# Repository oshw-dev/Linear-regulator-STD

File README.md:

# Linear-regulator-STD
Standard linear regulator

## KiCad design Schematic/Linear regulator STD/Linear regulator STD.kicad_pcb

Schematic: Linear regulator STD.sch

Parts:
C1, C3: 22uF; CP_EIA-3528-15_AVX-H_Pad1.50x2.35mm_HandSolder
C2: 100nF; C_0603_1608Metric_Pad1.05x0.95mm_HandSolder
C4: 10uF; C_1206_3216Metric_Pad1.42x1.75mm_HandSolder
D1, D2: 1N4002; D_SOD-123F
D3: LG_L29K-G2J1-24-Z; LED_0603_1608Metric; MPN LG L29K-G2J1-24-Z; Digi-Key_PN 475-2709-1-ND
J1: Screw_Terminal_01x04; PinHeader_1x04_P2.54mm_Horizontal
R1, R2: R; R_0603_1608Metric_Pad1.05x0.95mm_HandSolder
R3: 560; R_0603_1608Metric_Pad1.05x0.95mm_HandSolder
U1: LM317T; TO-220-3_Horizontal_TabDown; MPN LM317T; Digi-Key_PN 497-1575-5-ND

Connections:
/VIN: C1.1, C2.1, D1.1 (K), J1.1, U1.3 (IN)
/VOUT: C3.1, D1.2 (A), D2.1 (K), J1.4, R1.1, R3.1, U1.2 (OUT)
GND: C1.2, C2.2, C3.2, C4.2, D3.2, J1.2, J1.3, R2.2
unnamed: C4.1, D2.2 (A), R1.2, R2.1, U1.1 (ADJ)
unnamed: D3.1, R3.2

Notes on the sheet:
VO = ((R2 / R1) + 1) * 1.25 https://github.com/oshw-dev/Linear-regulator-STD/wiki 3.28V R1 = 240, R2 = 390 5.04V R1 = 330, R2 = 1000 11.83V R1 = 390, R2 = 3300
place near LM317
optional

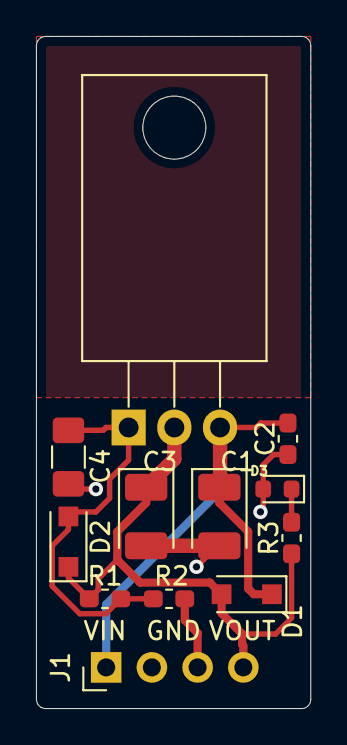
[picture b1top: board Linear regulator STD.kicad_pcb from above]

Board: 2 copper layers, 15.2 x 37.3 mm, 12 parts (0 on the bottom side), 5 nets.

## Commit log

2019-05-05 empty sheet
2019-05-05 copy-pasted request.md in specs.md
2019-05-05 ~1A spec
2019-05-05 ampere ~1A
2019-05-05 Texas instruments LM317 LM337
    found the chip that match the request, updated spec and notes
    added feature category
2019-05-05 added ONSEMI LM317 datasheet
2019-05-05 added D2PAK-3 package
2019-05-05 schematic alpha
2019-05-05 Annotation (alpha)
2019-05-05 cache.lib added
2019-05-05 wrong request
2019-05-05 REQUEST refactor
2019-05-05 SPECS refactor
2019-05-06 wrong request
    REQUEST refactor
    SPECS refactor
2019-05-06 TO220 package, C1 & c3 caps updated to 22uF Tantalum, C3 10uF ceramic
2019-05-06 Update Linear regulator STD.sch
    C3 name duplicate fix
2019-05-07 TO-220 vertical footprint
    added also 1x04 2.54 header
2019-05-07 label bug
2019-05-07 first PCB draft, PRO updated
2019-05-07 PCB update
    removed soldermask under the LM317
    round corners
2019-05-07 pin header 90 degree update
2019-05-07 added LED, silkscreen fix
2019-05-07 partial route
    work in progress
2019-05-08 PCB routing
